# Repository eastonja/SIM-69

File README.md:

6809 based Retro Computing project.  Mini-ITX sized board with 6809 at 2Mhz, 32K/64K RAM, ROM, 8K-32K EEPROM,
20x4 LCD interface, 2 RS-232 Serial ports (6551), 4 8-bit parallel ports (6522), I2C interface(PCF 8584), 
RTC (via typical I2C module), 24LC256 serial EEPROM.
Can be used as a SBC for experimenting, or mounted in a mini-ITX case with Peter Hizalev's VT100 terminal
daughter board for a self contained computer.

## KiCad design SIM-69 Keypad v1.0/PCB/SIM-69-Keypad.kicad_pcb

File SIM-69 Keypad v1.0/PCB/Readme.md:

PCB and Gerber files for SIM-69 Keypad

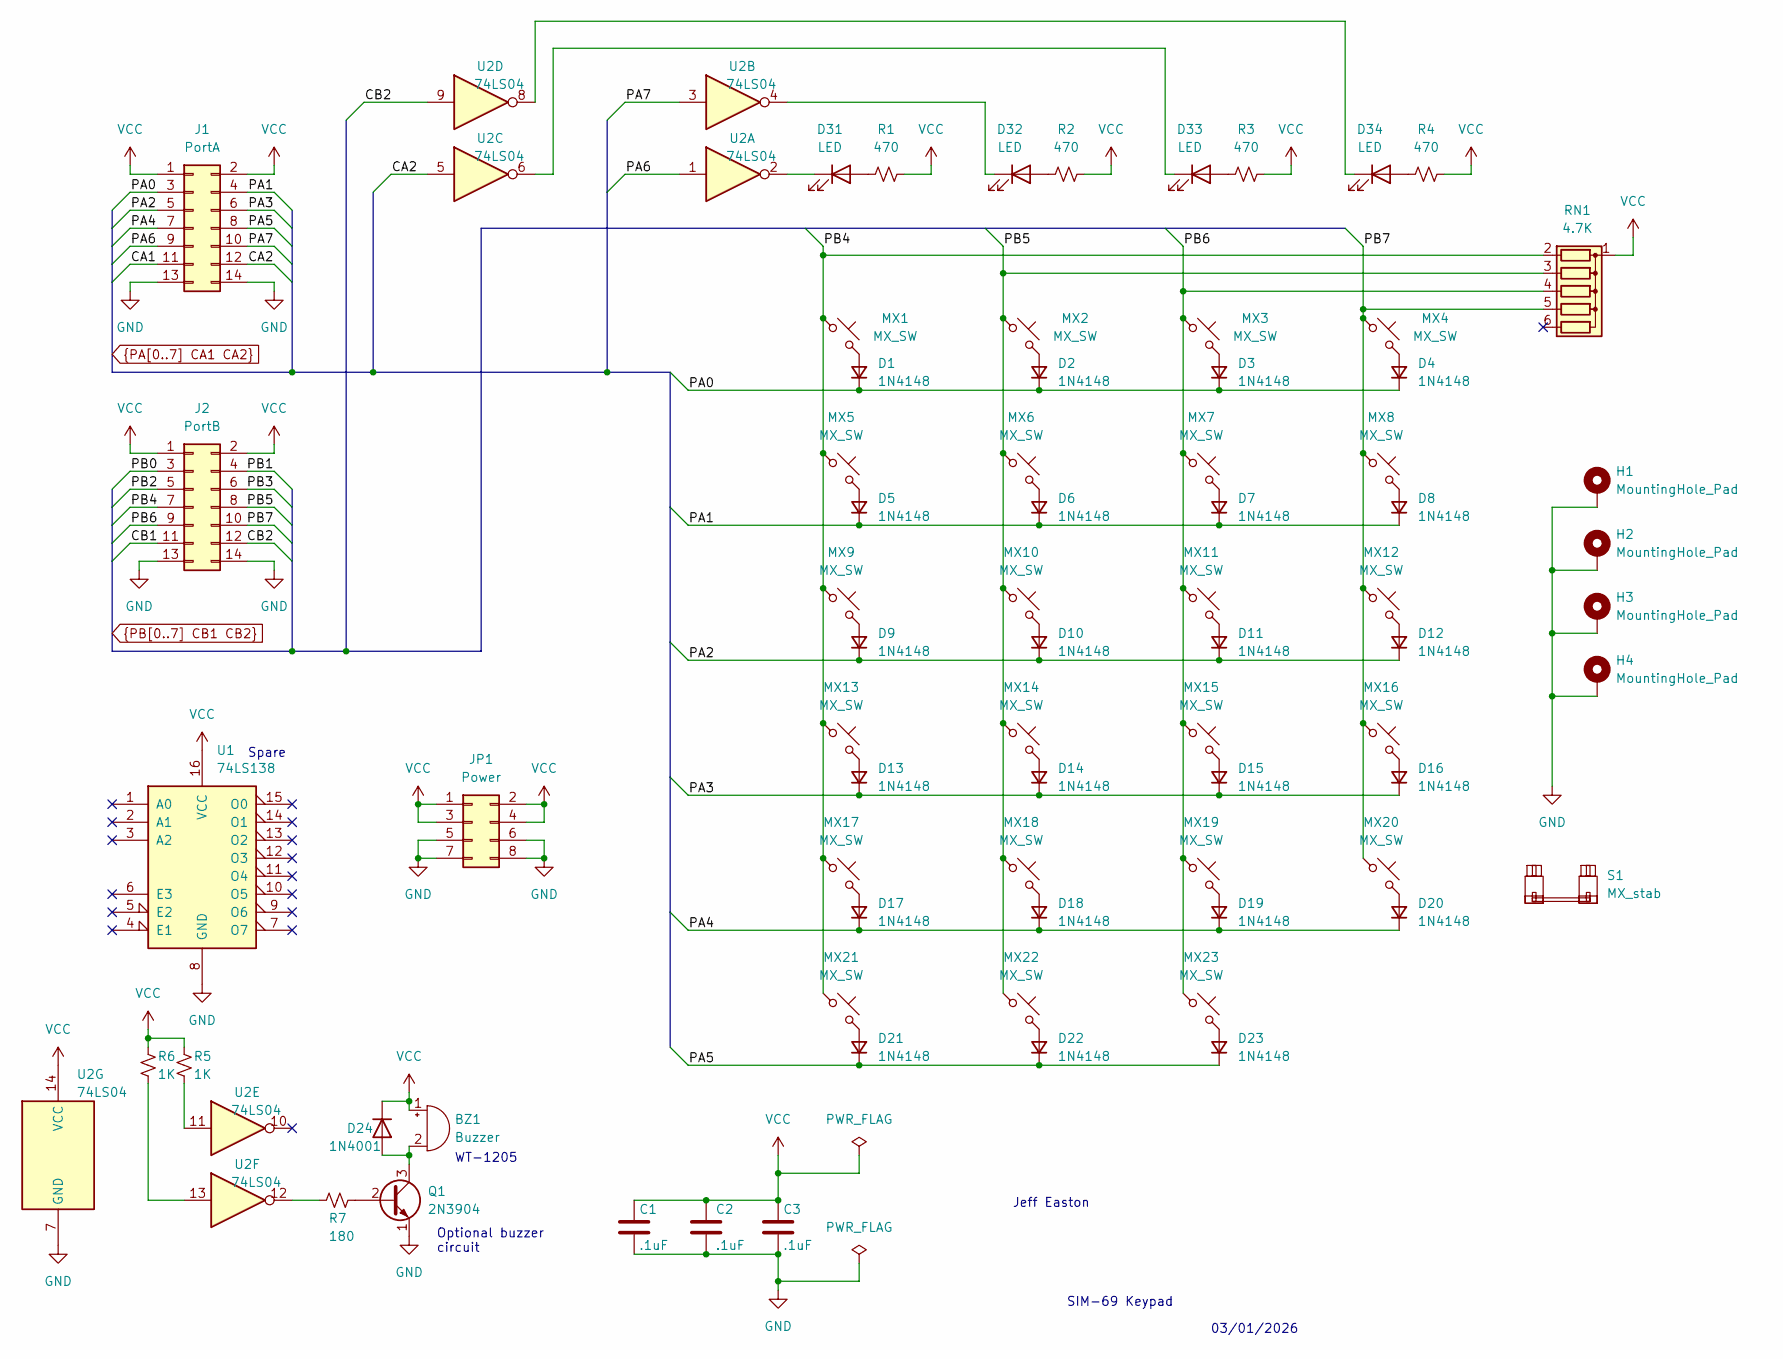
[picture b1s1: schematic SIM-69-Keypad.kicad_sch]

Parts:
BZ1: Buzzer; Buzzer_TDK_PS1240P02BT_D12.2mm_H6.5mm
C1, C2, C3: .1uF; C_Rect_L7.0mm_W2.0mm_P5.00mm
D1, D2, D3, D4, D5, D6, D7, D8, D9, D10, D11, D12, D13, D14, D15, D16, D17, D18, D19, D20, D21, D22, D23: 1N4148; D_DO-35_SOD27_P7.62mm_Horizontal
D24: 1N4001; D_DO-41_SOD81_P10.16mm_Horizontal
D31, D32, D33, D34: LED; LED_D3.0mm
H1, H2, H3, H4: MountingHole_Pad; MountingHole_3.7mm_Pad_TopBottom
J1: PortA; PinHeader_2x07_P2.54mm_Vertical
J2: PortB; PinHeader_2x07_P2.54mm_Vertical
JP1: Power; PinHeader_2x04_P2.54mm_Vertical
MX1, MX2, MX3, MX4, MX5, MX6, MX7, MX8, MX9, MX10, MX11, MX12, MX13, MX14, MX15, MX16, MX17, MX18, MX19, MX20, MX21, MX22, MX23: MX_SW; SW_MX_1u
Q1: 2N3904; TO-92_Inline
R1, R2, R3, R4: 470; R_Axial_DIN0207_L6.3mm_D2.5mm_P10.16mm_Horizontal
R5, R6: 1K; R_Axial_DIN0207_L6.3mm_D2.5mm_P10.16mm_Horizontal
R7: 180; R_Axial_DIN0207_L6.3mm_D2.5mm_P10.16mm_Horizontal
RN1: 4.7K; R_Array_SIP6
S1: MX_stab; STAB_MX_P_2u
U1: 74LS138; DIP-16_W7.62mm_Socket
U2: 74LS04; DIP-14_W7.62mm_Socket

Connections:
CA1: J1.11
CA2: J1.12, U2.5
CB1: J2.11
CB2: J2.12, U2.9
GND: C1.2, C2.2, C3.2, H1.1, H2.1, H3.1, H4.1, J1.13, J1.14, J2.13, J2.14, JP1.5, JP1.6, JP1.7, JP1.8, Q1.1 (E), U1.8 (GND), U2.7 (GND)
unnamed: BZ1.2 (+), D24.2 (A), Q1.3 (C)
unnamed: D1.2 (A), MX1.2
unnamed: D2.2 (A), MX2.2
unnamed: D3.2 (A), MX3.2
unnamed: D4.2 (A), MX4.2
unnamed: D5.2 (A), MX5.2
unnamed: D6.2 (A), MX6.2
unnamed: D7.2 (A), MX7.2
unnamed: D8.2 (A), MX8.2
unnamed: D9.2 (A), MX9.2
unnamed: D10.2 (A), MX10.2
unnamed: D11.2 (A), MX11.2
unnamed: D12.2 (A), MX12.2
unnamed: D13.2 (A), MX13.2
unnamed: D14.2 (A), MX14.2
unnamed: D15.2 (A), MX15.2
unnamed: D16.2 (A), MX16.2
unnamed: D17.2 (A), MX17.2
unnamed: D18.2 (A), MX18.2
unnamed: D19.2 (A), MX19.2
unnamed: D20.2 (A), MX20.2
unnamed: D21.2 (A), MX21.2
unnamed: D22.2 (A), MX22.2
unnamed: D23.2 (A), MX23.2
unnamed: D31.2 (A), R1.1
unnamed: D31.1 (K), U2.2
unnamed: D32.2 (A), R2.1
unnamed: D32.1 (K), U2.4
unnamed: D33.2 (A), R3.1
unnamed: D33.1 (K), U2.6
unnamed: D34.2 (A), R4.1
unnamed: D34.1 (K), U2.8
unnamed: Q1.2 (B), R7.1
unnamed: R5.2, U2.11
unnamed: R6.2, U2.13
unnamed: R7.2, U2.12
PA0: D1.1 (K), D2.1 (K), D3.1 (K), D4.1 (K), J1.3
PA1: D5.1 (K), D6.1 (K), D7.1 (K), D8.1 (K), J1.4
PA2: D9.1 (K), D10.1 (K), D11.1 (K), D12.1 (K), J1.5
PA3: D13.1 (K), D14.1 (K), D15.1 (K), D16.1 (K), J1.6
PA4: D17.1 (K), D18.1 (K), D19.1 (K), D20.1 (K), J1.7
PA5: D21.1 (K), D22.1 (K), D23.1 (K), J1.8
PA6: J1.9, U2.1
PA7: J1.10, U2.3
PB0: J2.3
PB1: J2.4
PB2: J2.5
PB3: J2.6
PB4: J2.7, MX1.1, MX5.1, MX9.1, MX13.1, MX17.1, MX21.1, RN1.2 (R1)
PB5: J2.8, MX2.1, MX6.1, MX10.1, MX14.1, MX18.1, MX22.1, RN1.3 (R2)
PB6: J2.9, MX3.1, MX7.1, MX11.1, MX15.1, MX19.1, MX23.1, RN1.4 (R3)
PB7: J2.10, MX4.1, MX8.1, MX12.1, MX16.1, MX20.1, RN1.5 (R4)
VCC: BZ1.1 (-), C1.1, C2.1, C3.1, D24.1 (K), J1.1, J1.2, J2.1, J2.2, JP1.1, JP1.2, JP1.3, JP1.4, R1.2, R2.2, R3.2, R4.2, R5.1, R6.1, RN1.1 (common), U1.16 (VCC), U2.14 (VCC)

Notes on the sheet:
Jeff Easton
Optional buzzer circuit
Spare
WT-1205
SIM-69 Keypad
03/01/2026

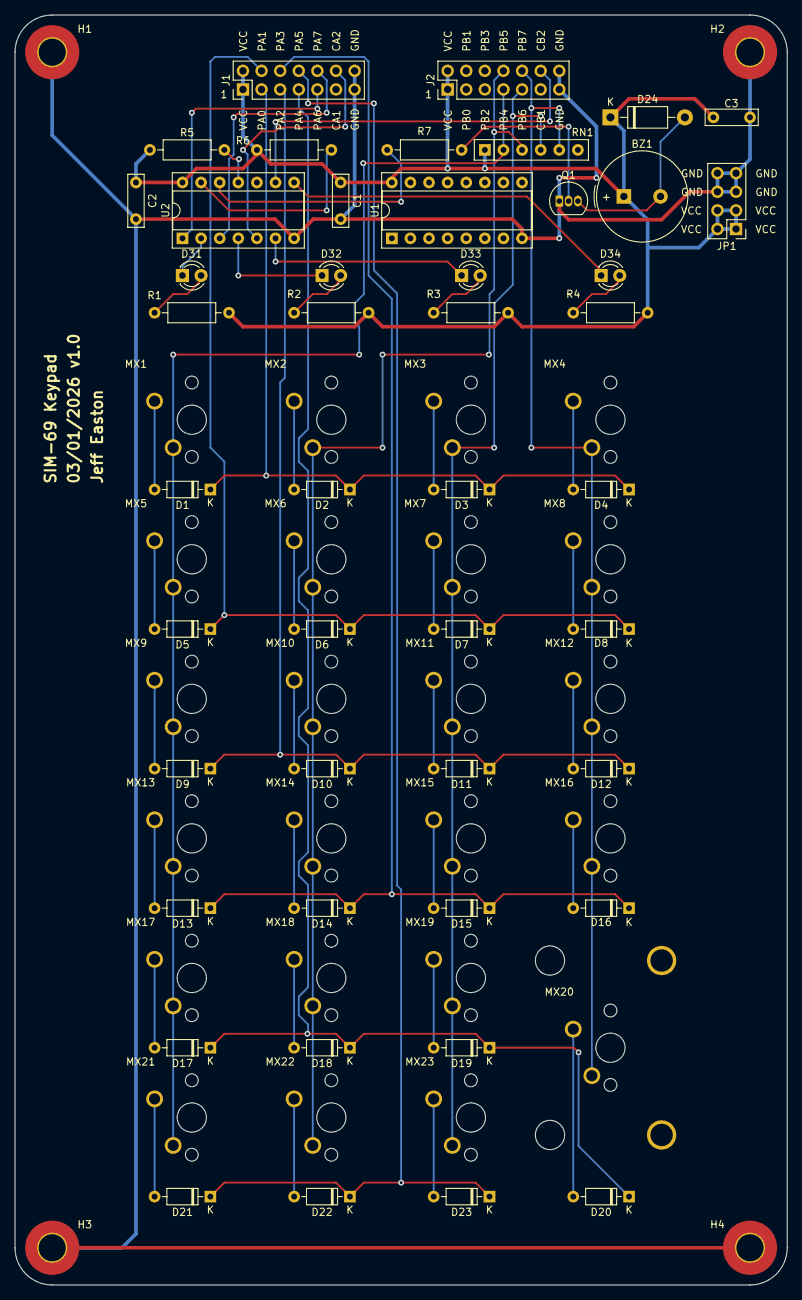
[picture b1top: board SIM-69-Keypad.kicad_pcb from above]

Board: 2 copper layers, 105.4 x 173.4 mm, 74 parts (0 on the bottom side), 52 nets.

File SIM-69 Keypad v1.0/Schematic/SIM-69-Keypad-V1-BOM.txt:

Component Count:	74						
Ref	Qnty	Value	Cmp name	Footprint	Description	Vendor	DNP
BZ1	1	Buzzer	Buzzer	Buzzer_Beeper:Buzzer_TDK_PS1240P02BT_D12.2mm_H6.5mm	"Buzzer, polarized"		
"C1, C2, C3"	3	.1uF	C	Capacitor_THT:C_Rect_L7.0mm_W2.0mm_P5.00mm	Unpolarized capacitor		
D1 through D23	23	1N4148	D_Small	Diode_THT:D_DO-35_SOD27_P7.62mm_Horizontal	"Diode, small symbol"		
D24	1	1N4001	1N4002_1	Diode_THT:D_DO-41_SOD81_P10.16mm_Horizontal	"100V 1A General Purpose Rectifier Diode, DO-41"		
"D31, D32, D33, D34"	4	LED	LED	LED_THT:LED_D3.0mm	Light emitting diode		
"H1, H2, H3, H4"	4	MountingHole_Pad	MountingHole_Pad	MountingHole:MountingHole_3.7mm_Pad_TopBottom	Mounting Hole with connection		
J1	1	PortA	Conn_02x07_Odd_Even	Connector_PinHeader_2.54mm:PinHeader_2x07_P2.54mm_Vertical	"Generic connector, double row, 02x07, odd/even pin numbering scheme (row 1 odd numbers, row 2 even numbers)"		
J2	1	PortB	Conn_02x07_Odd_Even	Connector_PinHeader_2.54mm:PinHeader_2x07_P2.54mm_Vertical	"Generic connector, double row, 02x07, odd/even pin numbering scheme (row 1 odd numbers, row 2 even numbers)"		
JP1	1	Power	Conn_02x04_Odd_Even	Connector_PinHeader_2.54mm:PinHeader_2x04_P2.54mm_Vertical	"Generic connector, double row, 02x04, odd/even pin numbering scheme (row 1 odd numbers, row 2 even numbers)"		
MX1 through MX23	23	MX_SW	MX_SW_solder	PCM_marbastlib-mx:SW_MX_1u	"Push button switch, normally open, two pins, 45° tilted. Cherry MX Brown"		
Q1	1	2N3904	2N3904	Package_TO_SOT_THT:TO-92_Inline	"0.2A Ic, 40V Vce, Small Signal NPN Transistor, TO-92"		
"R1, R2, R3, R4"	4	470	R_Small_US	Resistor_THT:R_Axial_DIN0207_L6.3mm_D2.5mm_P10.16mm_Horizontal	"Resistor, small US symbol"		1/4W 5% carbon film
"R5, R6"	2	1K	R_Small_US	Resistor_THT:R_Axial_DIN0207_L6.3mm_D2.5mm_P10.16mm_Horizontal	"Resistor, small US symbol"		1/4W 5% carbon film
R7	1	180	R_Small_US	Resistor_THT:R_Axial_DIN0207_L6.3mm_D2.5mm_P10.16mm_Horizontal	"Resistor, small US symbol"		1/4W 5% carbon film
RN1	1	4.7K	R_Network05	"Resistor_THT:R_Array_SIP6 (Optional, depending on 6522 VIA mfr)"	"5 resistor network, star topology, bussed resistors, small symbol"		
S1	1	MX_stab	MX_stab	"PCM_marbastlib-mx:STAB_MX_P_2u, DUROCK Stabilizer V3 PCB Mount"	Cherry MX-style stabilizer	Amazon	
U1	1	74LS138	74LS138	Package_DIP:DIP-16_W7.62mm_Socket (Optional/ Spare)	Decoder 3 to 8 active low outputs		
U2	1	74LS04	74LS04	Package_DIP:DIP-14_W7.62mm_Socket	Hex Inverter		
							
			PCB	Sim-69 Keypad base PCB		JLCPCB	https://jlcpcb.com/
			Plate	"Nyquist Plate, Black FR4 (optional)"		Keebio	https://keeb.io/products/nyquist-case-plates
			2x7 ribbon cable/conn	"2x7 IDC dual row female connectors, 14 con. Ribbon cable"		Jameco/Amazon	
			KeyCaps	"DSA Flex Keycaps, Hexidecimal set and Numpad Modifier set in Biege"		Signature Plastics	https://spkeyboards.com/products/dsa-flex-sublimated-keycaps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

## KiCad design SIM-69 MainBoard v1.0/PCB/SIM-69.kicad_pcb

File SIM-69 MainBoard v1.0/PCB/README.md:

PCB and Gerber files for SIM-69

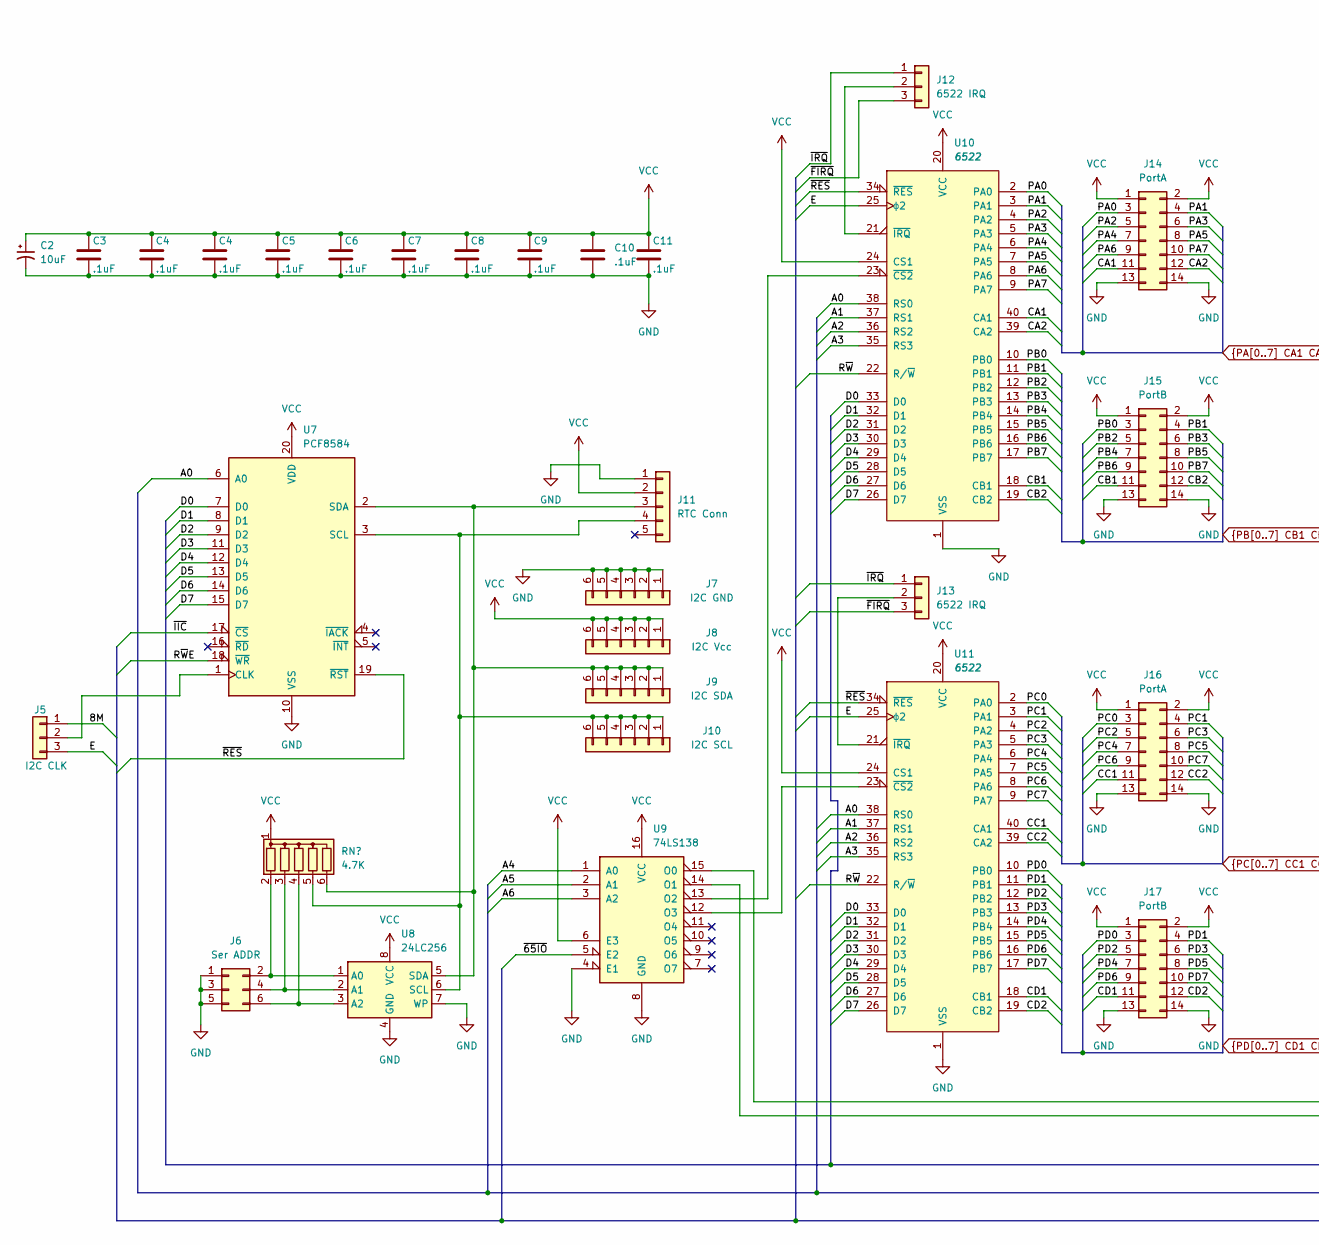
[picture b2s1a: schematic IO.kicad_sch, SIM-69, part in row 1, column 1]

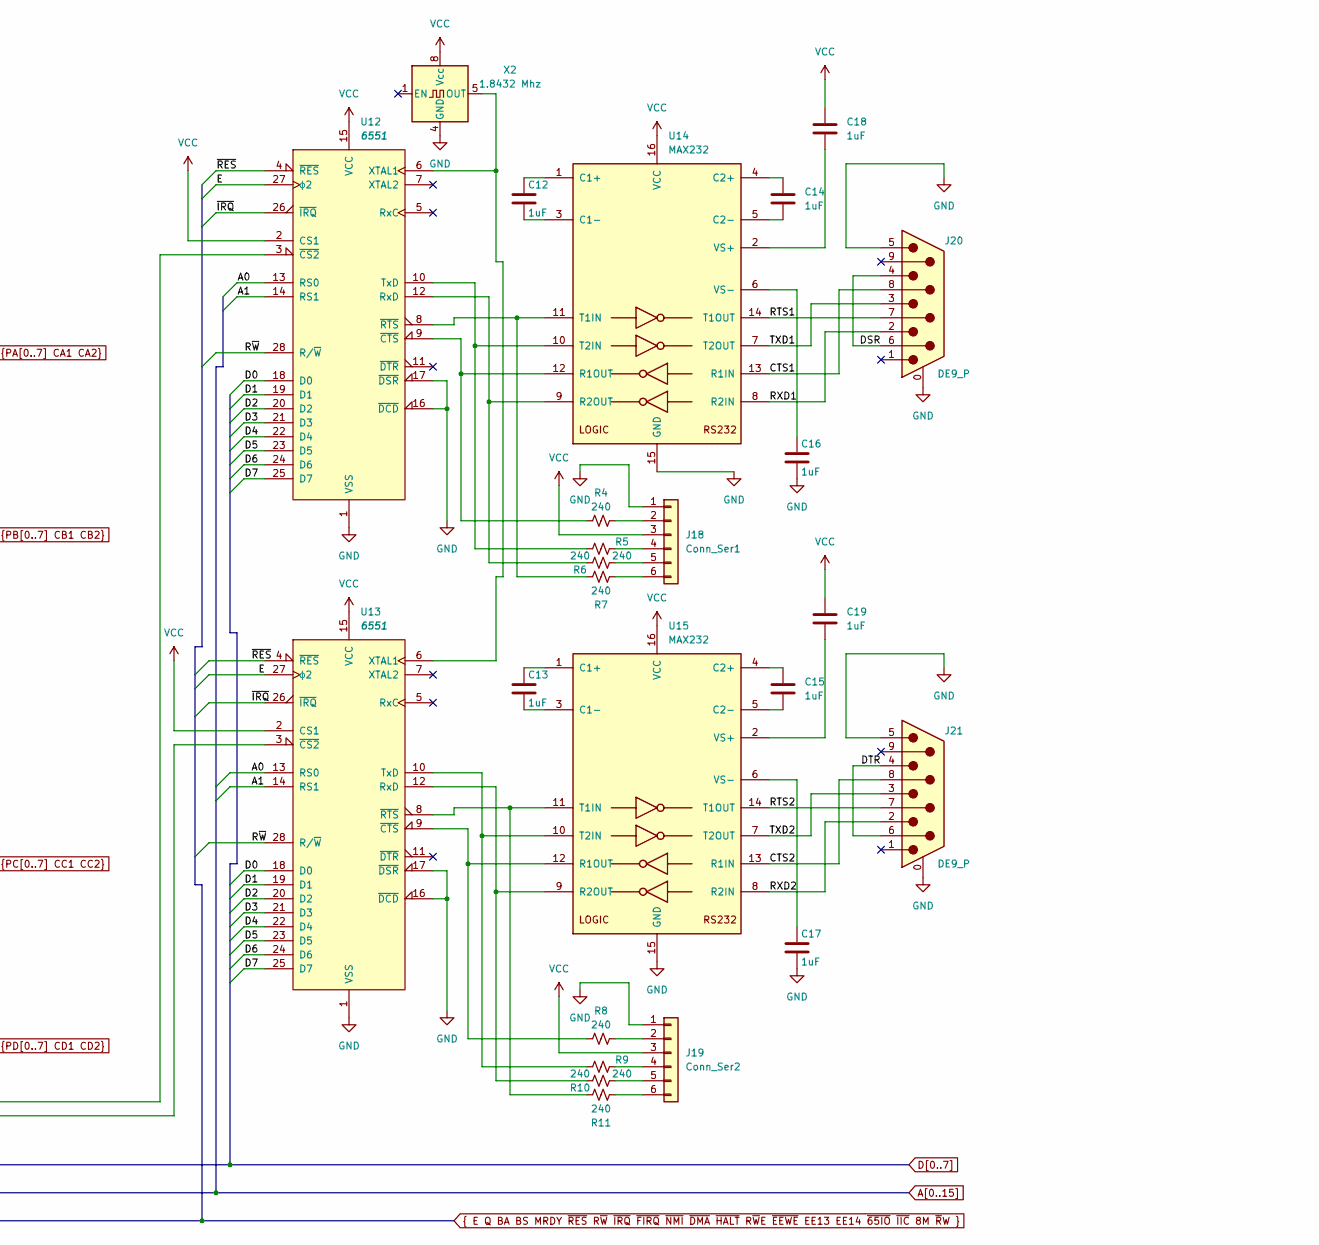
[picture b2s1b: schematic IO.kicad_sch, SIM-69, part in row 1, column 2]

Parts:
C2: 10uF; CP_Radial_Tantal_D4.5mm_P2.50mm
C3, C4, C5, C6, C7, C8, C9, C10, C11: .1uF; C_Rect_L7.0mm_W2.0mm_P5.00mm
C12, C13, C14, C15, C16, C17, C18, C19: 1uF; C_Rect_L7.0mm_W2.0mm_P5.00mm
J5: I2C CLK; PinHeader_1x03_P2.54mm_Vertical
J6: Ser ADDR; PinHeader_2x03_P2.54mm_Vertical
J7: I2C GND; PinSocket_1x06_P2.54mm_Vertical
J8: I2C Vcc; PinSocket_1x06_P2.54mm_Vertical
J9: I2C SDA; PinSocket_1x06_P2.54mm_Vertical
J10: I2C SCL; PinSocket_1x06_P2.54mm_Vertical
J11: RTC Conn; PinHeader_1x05_P2.54mm_Vertical
J12, J13: 6522 IRQ; PinHeader_1x03_P2.54mm_Vertical
J14, J16: PortA; PinHeader_2x07_P2.54mm_Vertical
J15, J17: PortB; PinHeader_2x07_P2.54mm_Vertical
J18: Conn_Ser1; PinHeader_1x06_P2.54mm_Vertical
J19: Conn_Ser2; PinHeader_1x06_P2.54mm_Vertical
J20, J21: DE9_P; DSUB-9_Male_Horizontal_P2.77x2.84mm_EdgePinOffset7.70mm_Hou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
R4, R5, R6, R7, R8, R9, R10, R11: 240; R_Axial_DIN0207_L6.3mm_D2.5mm_P10.16mm_Horizontal
RN3: 4.7K; R_Array_SIP6
U7: PCF8584; DIP-20_W7.62mm
U8: 24LC256; DIP-8_W7.62mm_Socket
U9: 74LS138; DIP-16_W7.62mm_Socket
U10, U11: 6522; DIP-40_W15.24mm_Socket
U12, U13: 6551; DIP-28_W15.24mm_Socket
U14, U15: MAX232; DIP-16_W7.62mm_Socket
X2: 1.8432 Mhz; Oscillator_DIP-8

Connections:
8M: J5.1; also elsewhere on the board
/IO/CTS1: J20.8, U14.13 (R1IN)
/IO/CTS2: J21.8, U15.13 (R1IN)
/IO/DSR: J20.4, J20.6
/IO/DTR: J21.4, J21.6
/IO/RTS1: J20.7, U14.14 (T1OUT)
/IO/RTS2: J21.7, U15.14 (T1OUT)
/IO/RXD1: J20.2, U14.8 (R2IN)
/IO/RXD2: J21.2, U15.8 (R2IN)
/IO/TXD1: J20.3, U14.7 (T2OUT)
/IO/TXD2: J21.3, U15.7 (T2OUT)
A0: U7.6 (A0), U10.38 (RS0), U11.38 (RS0), U12.13 (RS0), U13.13 (RS0); also elsewhere on the board
A1: U10.37 (RS1), U11.37 (RS1), U12.14 (RS1), U13.14 (RS1); also elsewhere on the board
A2: U10.36 (RS2), U11.36 (RS2); also elsewhere on the board
A3: U10.35 (RS3), U11.35 (RS3); also elsewhere on the board
A4: U9.1 (A0); also elsewhere on the board
A5: U9.2 (A1); also elsewhere on the board
A6: U9.3 (A2); also elsewhere on the board
CA1: J14.11, U10.40 (CA1)
CA2: J14.12, U10.39 (CA2)
CB1: J15.11, U10.18 (CB1)
CB2: J15.12, U10.19 (CB2)
CC1: J16.11, U11.40 (CA1)
CC2: J16.12, U11.39 (CA2)
CD1: J17.11, U11.18 (CB1)
CD2: J17.12, U11.19 (CB2)
D0: U7.7 (D0), U10.33 (D0), U11.33 (D0), U12.18 (D0), U13.18 (D0); also elsewhere on the board
D1: U7.8 (D1), U10.32 (D1), U11.32 (D1), U12.19 (D1), U13.19 (D1); also elsewhere on the board
D2: U7.9 (D2), U10.31 (D2), U11.31 (D2), U12.20 (D2), U13.20 (D2); also elsewhere on the board
D3: U7.11 (D3), U10.30 (D3), U11.30 (D3), U12.21 (D3), U13.21 (D3); also elsewhere on the board
D4: U7.12 (D4), U10.29 (D4), U11.29 (D4), U12.22 (D4), U13.22 (D4); also elsewhere on the board
D5: U7.13 (D5), U10.28 (D5), U11.28 (D5), U12.23 (D5), U13.23 (D5); also elsewhere on the board
D6: U7.14 (D6), U10.27 (D6), U11.27 (D6), U12.24 (D6), U13.24 (D6); also elsewhere on the board
D7: U7.15 (D7), U10.26 (D7), U11.26 (D7), U12.25 (D7), U13.25 (D7); also elsewhere on the board
E: J5.3, U10.25 (ϕ2), U11.25 (ϕ2), U12.27 (ϕ2), U13.27 (ϕ2); also elsewhere on the board
unnamed: J5.2, U7.1 (CLK)
unnamed: J6.2, RN3.2 (R1), U8.1 (A0)
unnamed: J6.4, RN3.3 (R2), U8.2 (A1)
unnamed: J6.6, RN3.4 (R3), U8.3 (A2)
unnamed: J10.1, J10.2, J10.3, J10.4, J10.5, J10.6, J11.4, RN3.5 (R4), U7.3 (SCL), U8.6 (SCL)
unnamed: J9.1, J9.2, J9.3, J9.4, J9.5, J9.6, J11.3, RN3.6 (R5), U7.2 (SDA), U8.5 (SDA)
unnamed: J12.2, U10.21 (~IRQ)
unnamed: J18.2, R4.2
unnamed: J18.4, R5.2
unnamed: J18.5, R6.2
unnamed: J18.6, R7.2
unnamed: J19.2, R8.2
unnamed: J19.4, R9.2
unnamed: J19.5, R10.2
unnamed: J19.6, R11.2
unnamed: U9.13 (O2), U10.23 (~CS2)
unnamed: U9.12 (O3), U11.23 (~CS2)
unnamed: R6.1, U12.12 (RxD), U14.9 (R2OUT)
unnamed: R5.1, U12.10 (TxD), U14.10 (T2IN)
unnamed: U12.6 (XTAL1), U13.6 (XTAL1), X2.5 (OUT)
unnamed: U9.15 (O0), U12.3 (~CS2)
unnamed: R4.1, U12.9 (~CTS), U14.12 (R1OUT)
unnamed: R7.1, U12.8 (~RTS), U14.11 (T1IN)
unnamed: R10.1, U13.12 (RxD), U15.9 (R2OUT)
unnamed: R9.1, U13.10 (TxD), U15.10 (T2IN)
unnamed: U9.14 (O1), U13.3 (~CS2)
unnamed: R8.1, U13.9 (~CTS), U15.12 (R1OUT)
unnamed: R11.1, U13.8 (~RTS), U15.11 (T1IN)
unnamed: C12.1, U14.1 (C1+)
unnamed: C12.2, U14.3 (C1-)
unnamed: C14.1, U14.4 (C2+)
unnamed: C14.2, U14.5 (C2-)
unnamed: C18.2, U14.2 (VS+)
unnamed: C16.1, U14.6 (VS-)
unnamed: C13.1, U15.1 (C1+)
unnamed: C13.2, U15.3 (C1-)
unnamed: C15.1, U15.4 (C2+)
unnamed: C15.2, U15.5 (C2-)
unnamed: C19.2, U15.2 (VS+)
unnamed: C17.1, U15.6 (VS-)
PA0: J14.3, U10.2 (PA0)
PA1: J14.4, U10.3 (PA1)
PA2: J14.5, U10.4 (PA2)
PA3: J14.6, U10.5 (PA3)
PA4: J14.7, U10.6 (PA4)
PA5: J14.8, U10.7 (PA5)
PA6: J14.9, U10.8 (PA6)
PA7: J14.10, U10.9 (PA7)
PB0: J15.3, U10.10 (PB0)
PB1: J15.4, U10.11 (PB1)
PB2: J15.5, U10.12 (PB2)
PB3: J15.6, U10.13 (PB3)
PB4: J15.7, U10.14 (PB4)
PB5: J15.8, U10.15 (PB5)
PB6: J15.9, U10.16 (PB6)
PB7: J15.10, U10.17 (PB7)
PC0: J16.3, U11.2 (PA0)
PC1: J16.4, U11.3 (PA1)
PC2: J16.5, U11.4 (PA2)
PC3: J16.6, U11.5 (PA3)
PC4: J16.7, U11.6 (PA4)
PC5: J16.8, U11.7 (PA5)
PC6: J16.9, U11.8 (PA6)
PC7: J16.10, U11.9 (PA7)
PD0: J17.3, U11.10 (PB0); also elsewhere on the board
PD1: J17.4, U11.11 (PB1); also elsewhere on the board
PD2: J17.5, U11.12 (PB2); also elsewhere on the board
PD3: J17.6, U11.13 (PB3)
PD4: J17.7, U11.14 (PB4)
PD5: J17.8, U11.15 (PB5)
PD6: J17.9, U11.16 (PB6)
PD7: J17.10, U11.17 (PB7)
R~W: U10.22 (R/~W), U11.22 (R/~W), U12.28 (R/~W), U13.28 (R/~W); also elsewhere on the board
R~WE: U7.18 (~WR); also elsewhere on the board
VCC: C2.1, C3.1, C4.1, C5.1, C6.1, C7.1, C8.1, C9.1, C10.1, C11.1, C18.1, C19.1, J8.1, J8.2, J8.3, J8.4, J8.5, J8.6, J11.2, J14.1, J14.2, J15.1, J15.2, J16.1, J16.2, J17.1, J17.2, J18.3, J19.3, RN3.1 (common), U7.20 (VDD), U8.8 (VCC), U9.6 (E3), U9.16 (VCC), U10.20 (VCC), U10.24 (CS1), U11.20 (VCC), U11.24 (CS1), U12.2 (CS1), U12.15 (VCC), U13.2 (CS1), U13.15 (VCC), U14.16 (VCC), U15.16 (VCC), X2.8 (Vcc); also elsewhere on the board
~65IO: U9.5 (E2); also elsewhere on the board
~IIC: U7.17 (~CS); also elsewhere on the board
~RES: U7.19 (~RST), U10.34 (~RES), U11.34 (~RES), U12.4 (~RES), U13.4 (~RES); also elsewhere on the board

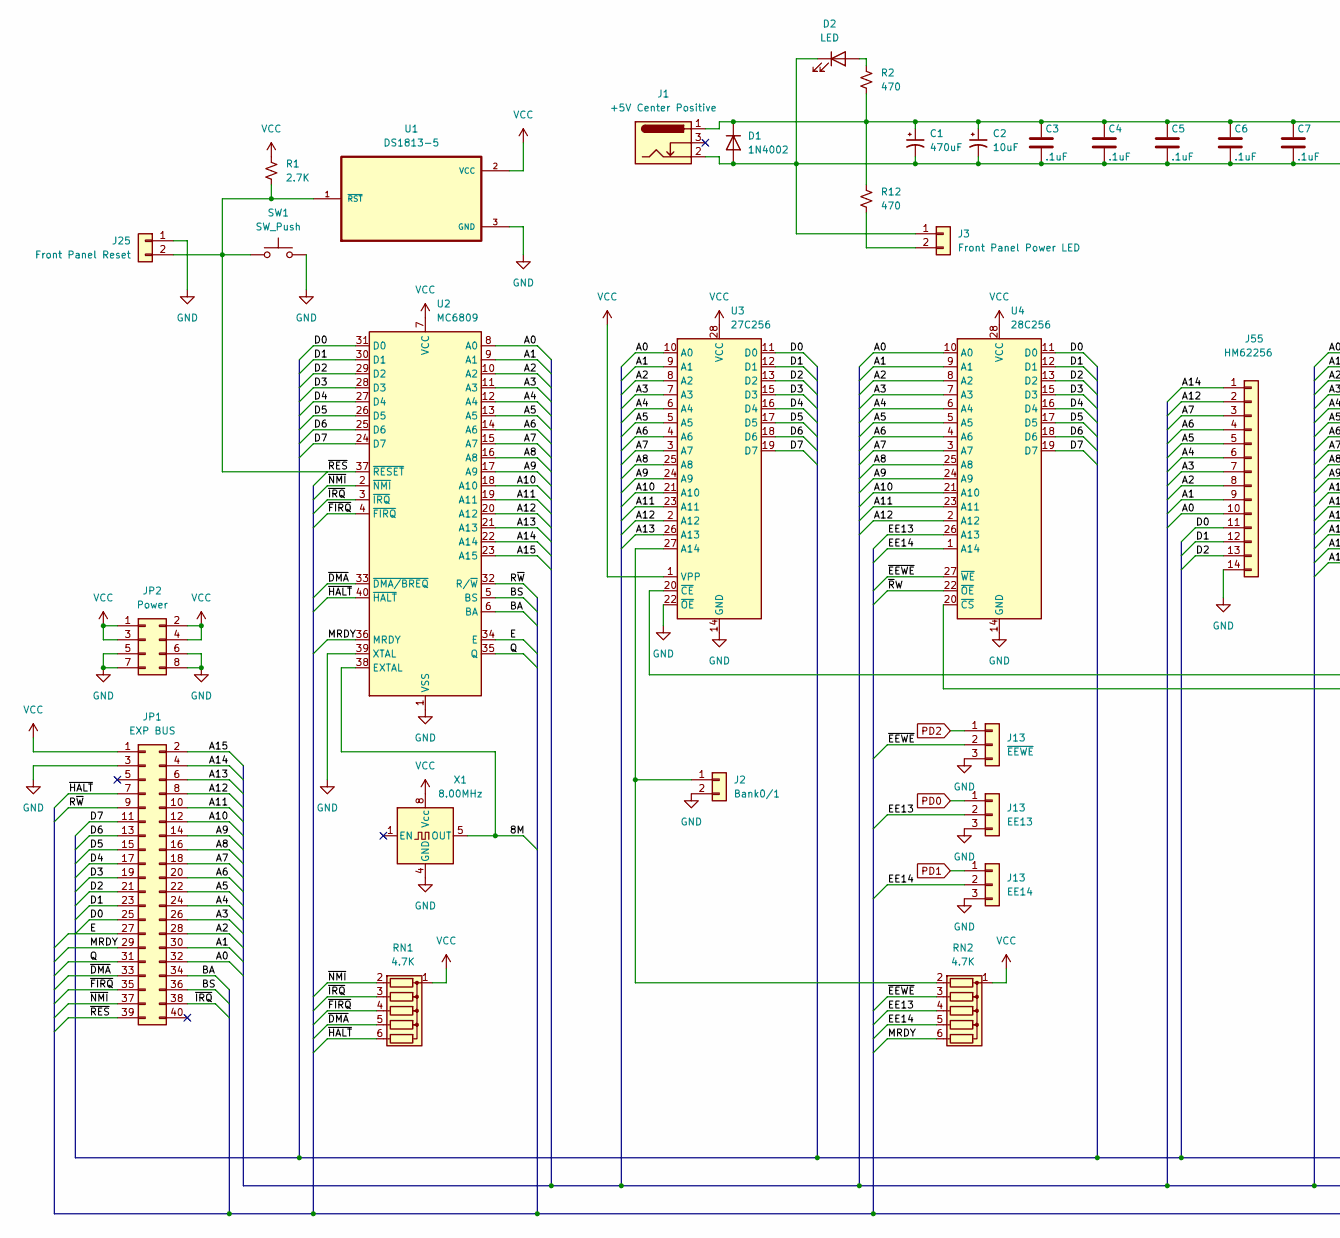
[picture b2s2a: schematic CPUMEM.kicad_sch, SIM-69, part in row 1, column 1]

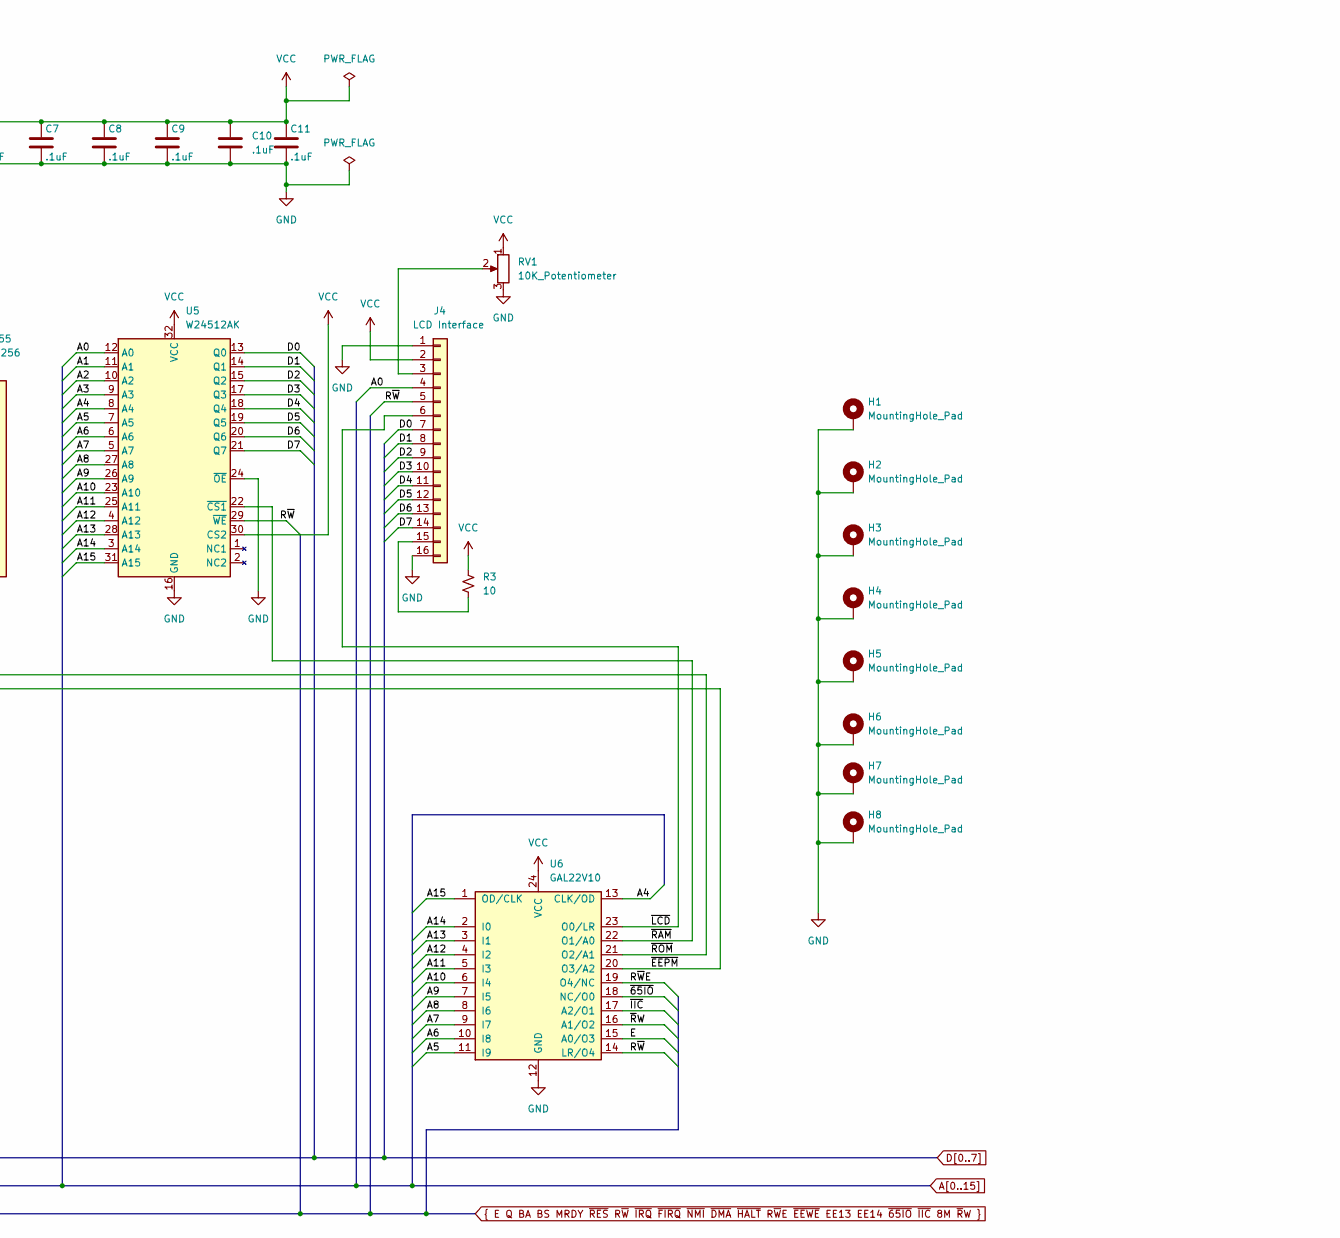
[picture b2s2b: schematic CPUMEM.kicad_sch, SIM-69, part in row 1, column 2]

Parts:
C1: 470uF; CP_Radial_D5.0mm_P2.50mm
C2: 10uF; CP_Radial_Tantal_D4.5mm_P2.50mm
C3, C4, C5, C6, C7, C8, C9, C10, C11: .1uF; C_Rect_L7.0mm_W2.0mm_P5.00mm
D1: 1N4002; D_DO-41_SOD81_P10.16mm_Horizontal
D2: LED; LED_D3.0mm
H1, H2, H3, H4, H5, H6, H7, H8: MountingHole_Pad; MountingHole_3.7mm_Pad_TopBottom
J1: +5V Center Positive; BarrelJack_Horizontal
J2: Bank0/1; PinSocket_1x02_P2.54mm_Vertical
J3: Front Panel Power LED; PinSocket_1x02_P2.54mm_Vertical
J4: LCD Interface; PinSocket_1x16_P2.54mm_Vertical
J13: EE14; PinHeader_1x03_P2.54mm_Vertical
J25: Front Panel Reset; PinSocket_1x02_P2.54mm_Vertical
J55: HM62256; PinSocket_1x14_P2.54mm_Vertical
JP1: EXP BUS; IDC-Header_2x20_P2.54mm_Vertical
JP2: Power; IDC-Header_2x04_P2.54mm_Vertical
R1: 2.7K; R_Axial_DIN0207_L6.3mm_D2.5mm_P10.16mm_Horizontal
R2, R12: 470; R_Axial_DIN0207_L6.3mm_D2.5mm_P10.16mm_Horizontal
R3: 10; R_Axial_DIN0207_L6.3mm_D2.5mm_P10.16mm_Horizontal
RN1, RN2: 4.7K; R_Array_SIP6
RV1: 10K_Potentiometer; Potentiometer_Vishay_T73YP_Vertical
SW1: SW_Push; SW_Tactile_SPST_Angled_PTS645Vx58-2LFS
U1: DS1813-5; TO-92
U2: MC6809; DIP-40_W15.24mm_Socket
U3: 27C256; DIP-28_W15.24mm_Socket
U4: 28C256; DIP-28_W15.24mm_Socket
U5: W24512AK; DIP-32_W7.62mm
U6: GAL22V10; DIP-24_W7.62mm_Socket
X1: 8.00MHz; Oscillator_DIP-8

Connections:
8M: U2.38 (EXTAL), X1.5 (OUT); also elsewhere on the board
/CPU Memory/~EEPM: U4.20 (~CS), U6.20 (O3/A2)
/CPU Memory/~LCD: J4.6, U6.23 (O0/LR)
/CPU Memory/~RAM: U5.22 (~CS1), U6.22 (O1/A0)
/CPU Memory/~ROM: U3.20 (~CE), U6.21 (O2/A1)
A0: J4.4, J55.10, JP1.32, U2.8 (A0), U3.10 (A0), U4.10 (A0), U5.12 (A0); also elsewhere on the board
A1: J55.9, JP1.30, U2.9 (A1), U3.9 (A1), U4.9 (A1), U5.11 (A1); also elsewhere on the board
A2: J55.8, JP1.28, U2.10 (A2), U3.8 (A2), U4.8 (A2), U5.10 (A2); also elsewhere on the board
A3: J55.7, JP1.26, U2.11 (A3), U3.7 (A3), U4.7 (A3), U5.9 (A3); also elsewhere on the board
A4: J55.6, JP1.24, U2.12 (A4), U3.6 (A4), U4.6 (A4), U5.8 (A4), U6.13 (CLK/OD); also elsewhere on the board
A5: J55.5, JP1.22, U2.13 (A5), U3.5 (A5), U4.5 (A5), U5.7 (A5), U6.11 (I9); also elsewhere on the board
A6: J55.4, JP1.20, U2.14 (A6), U3.4 (A6), U4.4 (A6), U5.6 (A6), U6.10 (I8); also elsewhere on the board
A7: J55.3, JP1.18, U2.15 (A7), U3.3 (A7), U4.3 (A7), U5.5 (A7), U6.9 (I7)
A8: JP1.16, U2.16 (A8), U3.25 (A8), U4.25 (A8), U5.27 (A8), U6.8 (I6)
A9: JP1.14, U2.17 (A9), U3.24 (A9), U4.24 (A9), U5.26 (A9), U6.7 (I5)
A10: JP1.12, U2.18 (A10), U3.21 (A10), U4.21 (A10), U5.23 (A10), U6.6 (I4)
A11: JP1.10, U2.19 (A11), U3.23 (A11), U4.23 (A11), U5.25 (A11), U6.5 (I3)
A12: J55.2, JP1.8, U2.20 (A12), U3.2 (A12), U4.2 (A12), U5.4 (A12), U6.4 (I2)
A13: JP1.6, U2.21 (A13), U3.26 (A13), U5.28 (A13), U6.3 (I1)
A14: J55.1, JP1.4, U2.22 (A14), U5.3 (A14), U6.2 (I0)
A15: JP1.2, U2.23 (A15), U5.31 (A15), U6.1 (OD/CLK)
BA: JP1.34, U2.6 (BA)
BS: JP1.36, U2.5 (BS)
D0: J4.7, J55.11, JP1.25, U2.31 (D0), U3.11 (D0), U4.11 (D0), U5.13 (Q0); also elsewhere on the board
D1: J4.8, J55.12, JP1.23, U2.30 (D1), U3.12 (D1), U4.12 (D1), U5.14 (Q1); also elsewhere on the board
D2: J4.9, J55.13, JP1.21, U2.29 (D2), U3.13 (D2), U4.13 (D2), U5.15 (Q2); also elsewhere on the board
D3: J4.10, JP1.19, U2.28 (D3), U3.15 (D3), U4.15 (D3), U5.17 (Q3); also elsewhere on the board
D4: J4.11, JP1.17, U2.27 (D4), U3.16 (D4), U4.16 (D4), U5.18 (Q4); also elsewhere on the board
D5: J4.12, JP1.15, U2.26 (D5), U3.17 (D5), U4.17 (D5), U5.19 (Q5); also elsewhere on the board
D6: J4.13, JP1.13, U2.25 (D6), U3.18 (D6), U4.18 (D6), U5.20 (Q6); also elsewhere on the board
D7: J4.14, JP1.11, U2.24 (D7), U3.19 (D7), U4.19 (D7), U5.21 (Q7); also elsewhere on the board
E: JP1.27, U2.34 (E), U6.15 (A0/O3); also elsewhere on the board
MRDY: JP1.29, RN2.6 (R5), U2.36 (MRDY)
unnamed: D2.2 (A), R2.1
unnamed: J2.1, RN2.2 (R1), U3.27 (A14)
unnamed: J3.2, R12.2
unnamed: J4.3, RV1.2
unnamed: J4.15, R3.2
Q: JP1.31, U2.35 (Q)
R~W: J4.5, JP1.9, U2.32 (R/~W), U5.29 (~WE), U6.14 (LR/O4); also elsewhere on the board
R~WE: U6.19 (O4/NC); also elsewhere on the board
VCC: C1.1, C2.1, C3.1, C4.1, C5.1, C6.1, C7.1, C8.1, C9.1, C10.1, C11.1, D1.1 (K), J1.1, J4.2, JP1.1, JP2.1, JP2.2, JP2.3, JP2.4, R1.1, R2.2, R3.1, R12.1, RN1.1 (common), RN2.1 (common), RV1.1, U1.2 (VCC), U2.7 (VCC), U3.1 (VPP), U3.28 (VCC), U4.28 (VCC), U5.30 (CS2), U5.32 (VCC), U6.24 (VCC), X1.8 (Vcc); also elsewhere on the board
~65IO: U6.18 (NC/O0); also elsewhere on the board
~DMA: JP1.33, RN1.5 (R4), U2.33 (~DMA/BREQ)
~HALT: JP1.7, RN1.6 (R5), U2.40 (~HALT)
~IIC: U6.17 (A2/O1); also elsewhere on the board
~NMI: JP1.37, RN1.2 (R1), U2.2 (~NMI)
~RES: J25.2, JP1.39, R1.2, SW1.1, U1.1 (~RST), U2.37 (~RESET); also elsewhere on the board
~RW: U4.22 (~OE), U6.16 (A1/O2)

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
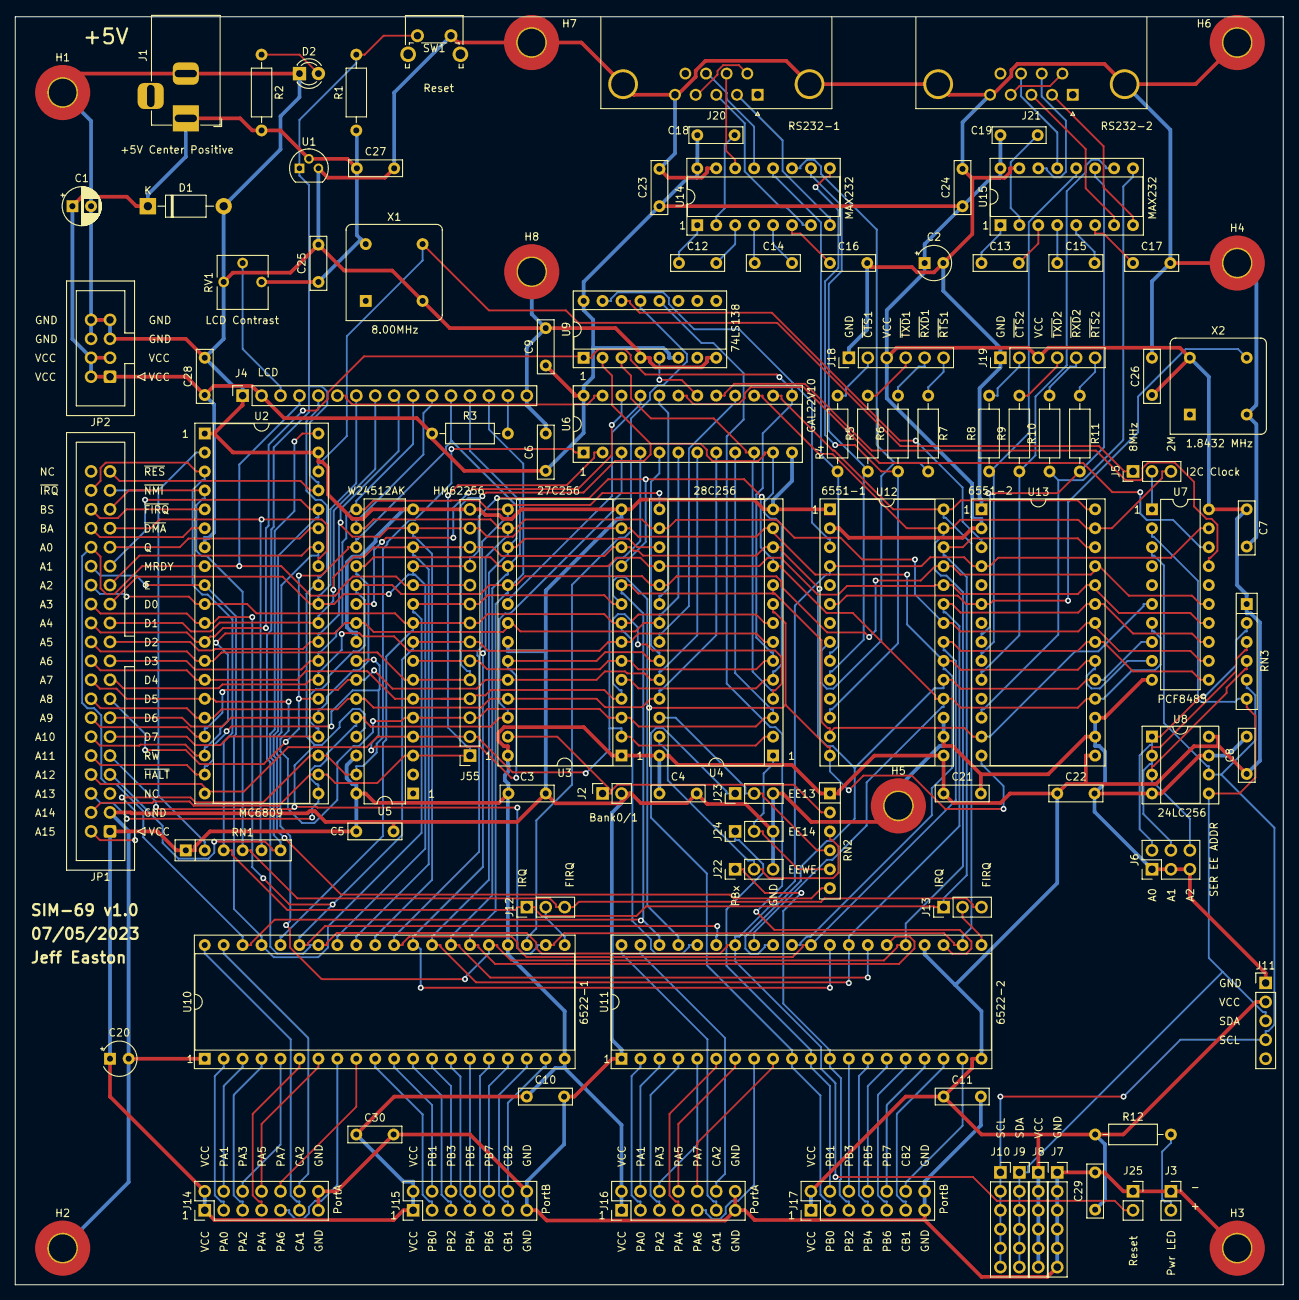
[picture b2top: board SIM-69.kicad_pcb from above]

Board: 2 copper layers, 170.0 x 170.0 mm, 102 parts (0 on the bottom side), 146 nets.

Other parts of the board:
C20: 10uF; CP_Radial_Tantal_D4.5mm_P2.50mm
C21, C22, C23, C24, C25, C26, C27, C29, C30: .1uF; C_Rect_L7.0mm_W2.0mm_P5.00mm
C28: ,1uF; C_Rect_L7.0mm_W2.0mm_P5.00mm
J22: ~{EEWE}; PinHeader_1x03_P2.54mm_Vertical
J23: EE13; PinHeader_1x03_P2.54mm_Vertical
J24: EE14; PinHeader_1x03_P2.54mm_Vertical

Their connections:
PD0: J23.1; also elsewhere on the board
PD1: J24.1; also elsewhere on the board
PD2: J22.1; also elsewhere on the board
VCC: C20.1, C21.1, C22.1, C23.1, C24.1, C25.1, C26.1, C27.1, C28.1, C29.1, C30.1; also elsewhere on the board

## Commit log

2023-07-30 Create README.md
    Description of the SIM-69 computer project
2023-07-30 Create v1.0
    Initial Release
2023-09-12 Add files via upload
    SmartBug v1.27a-s69 monitor rom
2023-09-13 Add files via upload
    OLED and RTC i2c demo program. reads time from real time clock and displays it on the oled screen
2026-04-16 rename
